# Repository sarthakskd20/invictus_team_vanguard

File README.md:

# Invictus Inventory Management System
> **Team Vanguard** | Electrolyte Solutions Hackathon

A full-stack, component-level inventory management system built with the B.L.A.S.T. protocol.

## 🚀 Quick Start

### Prerequisites
- **Node.js** (v18+)
- **PostgreSQL** (v15+) - [Installation Guide](docs/postgresql_setup.md)

### One-Click Setup
Run the automated launcher:
```bash
d:\invictus_hackathon\run_app.bat
```
This script will:
1. Check for required software
2. Install dependencies (frontend & backend)
3. Set up the database (schema + seed data)
4. Start the application

## 📚 Documentation
- [Implementation Plan](docs/implementation_plan.md)
- [PostgreSQL Setup Guide](docs/postgresql_setup.md)

## 🛠 Tech Stack
- **Frontend**: React, Vite, Chart.js, Lucide Icons
- **Backend**: Node.js, Express, PostgreSQL
- **Database**: PostgreSQL with Row-Level Locking

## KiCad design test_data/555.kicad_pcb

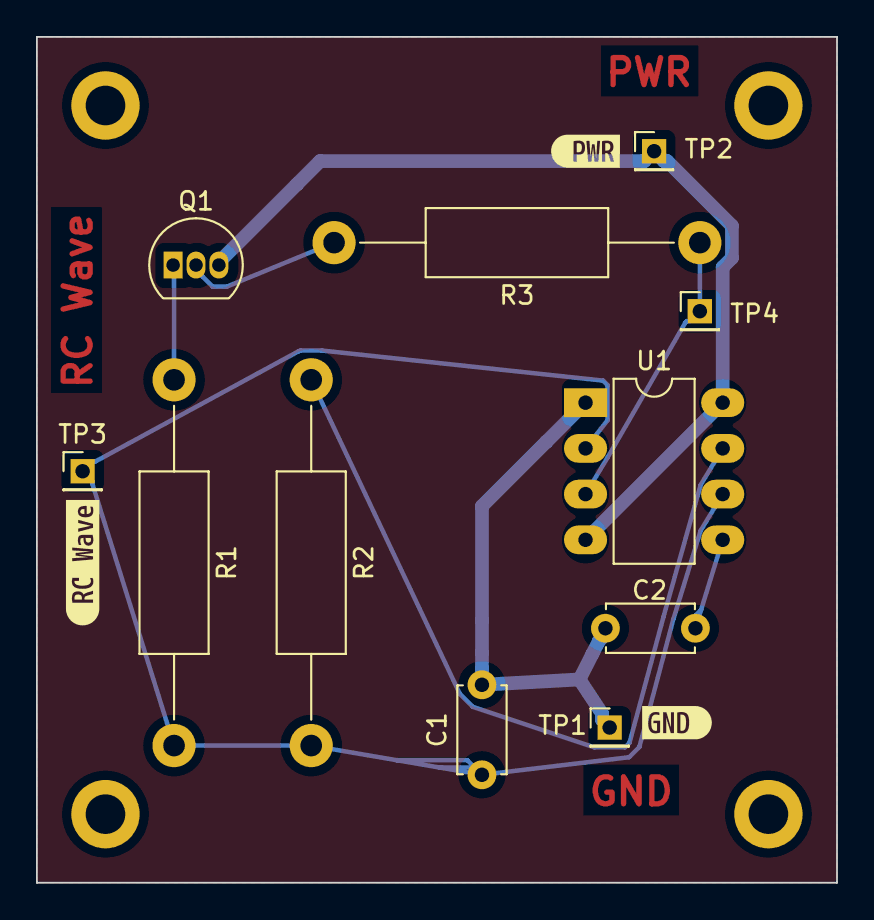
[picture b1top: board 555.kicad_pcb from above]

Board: 2 copper layers, 44.5 x 47.0 mm, 18 parts (0 on the bottom side), 8 nets.

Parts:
C1: 1uF; C_Disc_D4.7mm_W2.5mm_P5.00mm
C2: 0.01uF; C_Disc_D4.7mm_W2.5mm_P5.00mm
Mount1, Mount2, Mount3, Mount4: MountingHole_2.2mm_M2_ISO14580_Pad
Q1: 2N3904; TO-92_Inline
R1: 60K; R_Axial_DIN0411_L9.9mm_D3.6mm_P20.32mm_Horizontal
R2, R3: 100K; R_Axial_DIN0411_L9.9mm_D3.6mm_P20.32mm_Horizontal
TP1, TP2, TP3, TP4: TestPoint_Probe; PinHeader_1x01_P2.00mm_Vertical
U1: TLC555; DIP-8_W7.62mm_LongPads
kibuzzard-65C1C1B8: G***; kibuzzard-65C1C1B8
kibuzzard-65C251C9: G***; kibuzzard-65C251C9
kibuzzard-65C0921A: G***; kibuzzard-65C0921A

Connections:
/OUTPUT: R3.1, TP4.1, U1.3 (OUT)
/POWER: Q1.3 (C), TP2.1, U1.4 (~RESET), U1.8 (VDD)
/RC WAVE: C1.1, R1.2, R2.2, TP3.1, U1.2 (~TRIG), U1.6 (THRES)
GND: C1.2, C2.2, TP1.1, U1.1 (GND)
unnamed: Q1.2 (B), R3.2
unnamed: Q1.1 (E), R1.1
unnamed: C2.1, U1.5 (CONT)
unnamed: R2.1, U1.7 (DISCH)

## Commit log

2026-02-14 Update codebase with team vanguard resources
2026-02-14 Create Parsing Functionality Complete
2026-02-14 Add example environment configuration file
2026-02-14 feat: setup BLAST protocol artifacts and upgrade parsing skill
2026-02-14 feat: add Git Manager skill for flawless repo sync and management
2026-02-14 feat: add workflow agent skills (backend-architect, dx-optimizer, performance-engineer) and update implementation plan with user feedback
2026-02-14 feat: update implementation plan with all user feedback and add workflow agents
2026-02-14 feat: restore CAD import feature with Antigravity skillset workflow integration
2026-02-14 docs: extract implementation plan to markdown file
2026-02-14 feat: complete full-stack inventory management system - Backend: 7 controllers, 7 route files, 3 middleware, PostgreSQL schema - Frontend: 6 pages, industrial dark theme, auth context, Chart.js - Inc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
2026-02-14 fix: escape parentheses in run_app.bat to prevent syntax error
2026-02-14 feat: Implement schematic import preview and smart categorization
2026-02-15 Fix: Excel import column mapping and Report date filtering logic
2026-02-15 feat: Implement Missing Components Detection System & Fix Schematic Import
2026-02-15 feat: rewrite animated sidebar with inline styles and industrial theme
2026-02-15 feat: Add 18 new PCB types with BOM mappings
2026-02-15 MIT LICENCE
    updated mit licence
2026-02-15 feat: Fix UI contrast for shortages and improve numeric input UX
2026-02-15 fix: Ensure npm install runs in run_app.bat to prevent missing dependencies on pull
2026-02-15 fix: resolve all frontend build and lint errors
2026-02-20 feat: Frontend UI overhaul - Login page redesign with Three.js animated background - Post-login selection page with CardStack component - Dashboard dot-shader background and glowing card borders - Ba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
2026-02-21 Silk theme: redesigned selection cards with SVG art, improved fonts, buttons, sidebar styling, keyboard nav
